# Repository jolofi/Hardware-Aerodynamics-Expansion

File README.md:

# Hardware-Aerodynamics-Expansion

Hardware and Aerodynamics Expansion

This repository contains the mechanical and electrical design files for a Continuing Professional Development project at the University of Nottingham. The project encompasses custom aerodynamic surfacing and printed circuit board development.

Aerodynamic Surfacing

- Designed a performance enhancing front nosecone assembly using Autodesk Inventor.
- Incorporated a swept main plane, secondary flaps, and vertical endplates into the CAD model.
- Engineered the assembly geometry to optimize airflow and increase front tyre ground effect during cornering.

Printed Circuit Board Design

- Developed a highly size efficient custom printed circuit board using KiCad schematic capture and layout tools.
- Integrated a stable voltage divider and gain amplifier circuit directly into the board architecture.
- Selected and routed surface mount resistors alongside ceramic and electrolytic decoupling capacitors.
- Designed the electrical layout to create a stable reference voltage while actively mitigating high frequency electrical noise.

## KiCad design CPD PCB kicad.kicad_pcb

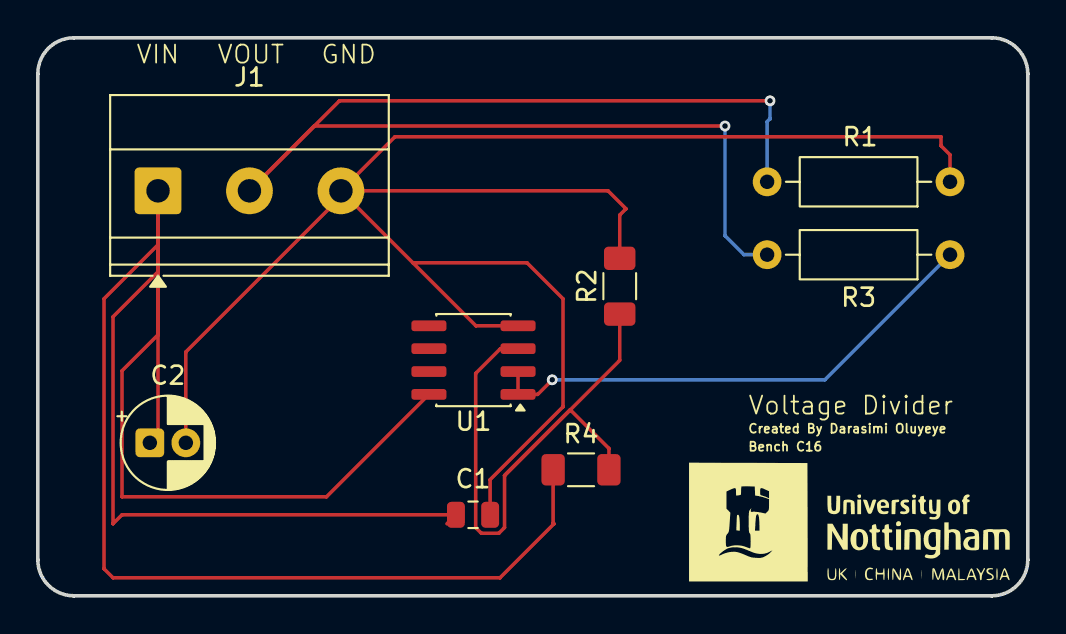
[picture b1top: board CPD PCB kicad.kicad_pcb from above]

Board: 2 copper layers, 55.0 x 31.0 mm, 8 parts (0 on the bottom side), 5 nets.

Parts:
C1: C; C_0805_2012Metric
C2: C_Polarized; CP_Radial_D5.0mm_P2.00mm
J1: Screw_Terminal_01x03; TerminalBlock_Phoenix_MKDS-1,5-3-5.08_1x03_P5.08mm_Horizont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
R1, R3: R; R_Axial_DIN0207_L6.3mm_D2.5mm_P10.16mm_Horizontal
R2: 560; R_1206_3216Metric_Pad1.30x1.75mm_HandSolder
R4: 840; R_1206_3216Metric_Pad1.30x1.75mm_HandSolder
U1: LM358; SOIC-8_3.9x4.9mm_P1.27mm

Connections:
+5V: C1.1, C2.1, J1.1, R4.1, U1.8 (V+)
GND: C1.2, C2.2, J1.3, R1.1, R2.2, U1.4 (V-)
unnamed: J1.2, R1.2, R3.2
unnamed: R2.1, R4.2, U1.3 (+)
unnamed: R3.1, U1.1, U1.2 (-)
